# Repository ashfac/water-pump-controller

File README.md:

# Water Pump controller

This repository contains two projects:

- [KiCAD schematics](https://gitea.odroid.hc/hobby-projects/water-pump-controller/src/branch/master/kicad)
- [Visual Studio Code Arduino application](https://gitea.odroid.hc/hobby-projects/water-pump-controller/src/branch/master/visual-studio-code)

## Schematics

## Board

## Prototype

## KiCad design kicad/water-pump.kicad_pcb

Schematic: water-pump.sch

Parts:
5V1: 5V; M02
AC-IN1: AC-IN; M02
AC-OUT1: AC-OUT; M02
AUX1: AUX; M02
C1: 0.1uF; C025-025X050
C2: 10uF; E2,5-5
CT1: CT; M02
D1: 1N4148DO35-7; DO35-7
D4: ZPD; DO35Z10
DC-IN1: DC-IN; M02
FLT1: FLT; M02
LCD1: LCD
LED1, LED2, LED3: LED
PB1: PB1; M02
PB2: PB2; M02
PT-220V1: PT-220V; M02
PT-IN1: PT-IN; M03
PWR1: LED
Q1: 2N3904; TO92-EBC
Q2, Q3: 2N3906; TO92-EBC
R1, R2, R5, R6, R7, R8, R9, R11: 1K; 0207_10
R3, R4, R10: 10K; 0207_10
R15: 100R; 0207_10
R16, R17: 100K; 0207_10
R18: 4K7; 0207_10
RELAY1: RELAYPTH; SRD-05VDC-SL-C
RELAY2: RELAY; M02
SR-4: SR-04; M02
SW1: SW; M02
U$1: ARDUINO-NANOV3; ARDUINO-NANO
U$2: BT-HC-05DEFAULT; BT-HC-05

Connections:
GND: 5V1.2, AUX1.1, C2.-, D4.A, DC-IN1.2, LCD1.GND, PB1.1, PB2.2, PT-IN1.3, PWR1.-, Q1.E, R4.1, R16.1, U$1.GND1, U$1.GND2, U$2.GND
unnamed: AC-IN1.1, AC-OUT1.2, PT-220V1.2, RELAY2.1
unnamed: AC-IN1.2, SW1.1
unnamed: AC-OUT1.1, PT-220V1.1, RELAY1.SWOPEN, SW1.2
unnamed: AUX1.2, U$1.A1
unnamed: C1.1, U$2.STATE
unnamed: C1.2, U$1.RST1
unnamed: C2.+, CT1.2, R15.1, R16.2, R17.1
unnamed: CT1.1, R15.2, R18.1
unnamed: D1.A, Q1.C, RELAY1.COIL1
unnamed: D4.C, R18.2, U$1.A6
unnamed: FLT1.1, U$1.A4
unnamed: FLT1.2, U$1.A5
unnamed: LCD1.CS, U$1.D10
unnamed: LCD1.D/C, U$1.D9
unnamed: LCD1.LED, LCD1.SD_SCK, LCD1.T_CLK, Q2.C
unnamed: LCD1.MISO, LCD1.SD_MISO, LCD1.T_DO, U$1.D12
unnamed: LCD1.MOSI, LCD1.SD_MOSI, LCD1.T_DIN, U$1.D11
unnamed: LCD1.RST, U$1.D8
unnamed: LCD1.SCK, U$1.D13
unnamed: LCD1.SD_CS, U$1.D4
unnamed: LCD1.T_CS, U$1.D7
unnamed: LCD1.T_IRQ, U$1.D3
unnamed: LED1.+, R6.1
unnamed: LED1.-, U$1.D5
unnamed: LED2.+, R7.1
unnamed: LED2.-, U$1.D0/RX, U$2.TXD
unnamed: LED3.+, R8.1
unnamed: LED3.-, U$1.D1/TX, U$2.RXD
unnamed: PB1.2, PB2.1, U$1.D2
unnamed: PT-IN1.2, U$1.A7
unnamed: PWR1.+, R5.1
unnamed: Q1.B, R1.1, R4.2
unnamed: Q2.B, R2.2, R3.1
unnamed: Q3.B, R9.2, R10.1
unnamed: Q3.C, SR-4.1
unnamed: R1.2, U$1.A0
unnamed: R2.1, U$1.D6
unnamed: R9.1, U$1.A2
unnamed: R11.1, SR-4.2
unnamed: R11.2, U$1.A3
unnamed: R17.2, U$1.5V (+5V)
unnamed: RELAY1.SWCOMMON, RELAY2.2
VCC: 5V1.1, D1.C, DC-IN1.1, LCD1.VCC, PT-IN1.1, Q2.E, Q3.E, R3.2, R5.2, R6.2, R7.2, R8.2, R10.2, RELAY1.COIL0, U$1.VIN, U$2.VCC

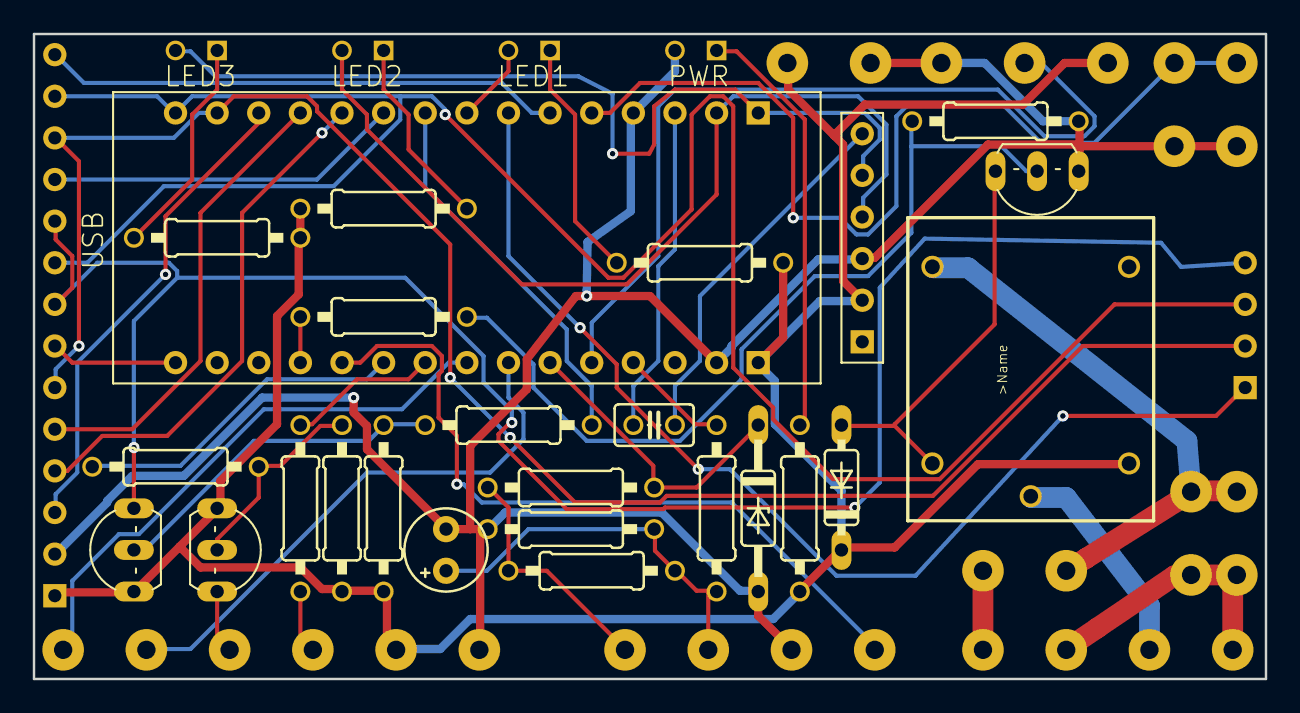
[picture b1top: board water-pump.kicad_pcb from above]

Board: 2 copper layers, 75.2 x 39.4 mm, 44 parts (0 on the bottom side), 44 nets.

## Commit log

2019-06-09 push schematics and source code
2019-06-09 restructure folders and files
2019-06-09 update gitignore
2019-06-09 apply gitignore
2019-06-09 add documents
2019-06-10 add pics to README.md
